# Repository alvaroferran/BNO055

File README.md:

# BNO055
#### 9DOF Absolute orientation sensor

&nbsp;

This repository contains the sensor board and a library for arduino. Both the board and the library are still under development and susceptible of improvement :)

#### BOARD

·The sensor works at 3.3V and can be used through UART or I2C by soldering the PS0 and PS1 pads below, as per the table below:

| PS1        | PS0           | Functionality  |
| ------------- |:-------------:| -----:|
| 0 | 0 | Standard/Fast I2C Interface|
| 0 | 1 |   HID over I2C |
| 1 | 0 |    UART Interface |
| 1 | 1 |    Reserved |

In order to be used with a 5V level microcontroller a 5V-3.3V level shifter must be used.

&nbsp;
·It has two possible, hardware-defined I2C addresses, which are selectable through a solder pad, as in the following table:

| ID PAD       | I2C Address           | ID  |
| ------------- |:-------------:| -----:|
| Not soldered | 0x28 | A |
| Soldered | 0x29 | B  |

&nbsp;

·The "I2C" pad enables the sensor's 4.7k pullup resistors. This pad should only be soldered if there were no other pullup resistors on the bus.

&nbsp;

#### LIBRARY

· To install the library simply copy the folder "BNO055" into your folder "sketchbook/libraries/".

&nbsp;
· In the "examples" subfolder a cheatsheet sketch is available which demonstrates how to read different data.

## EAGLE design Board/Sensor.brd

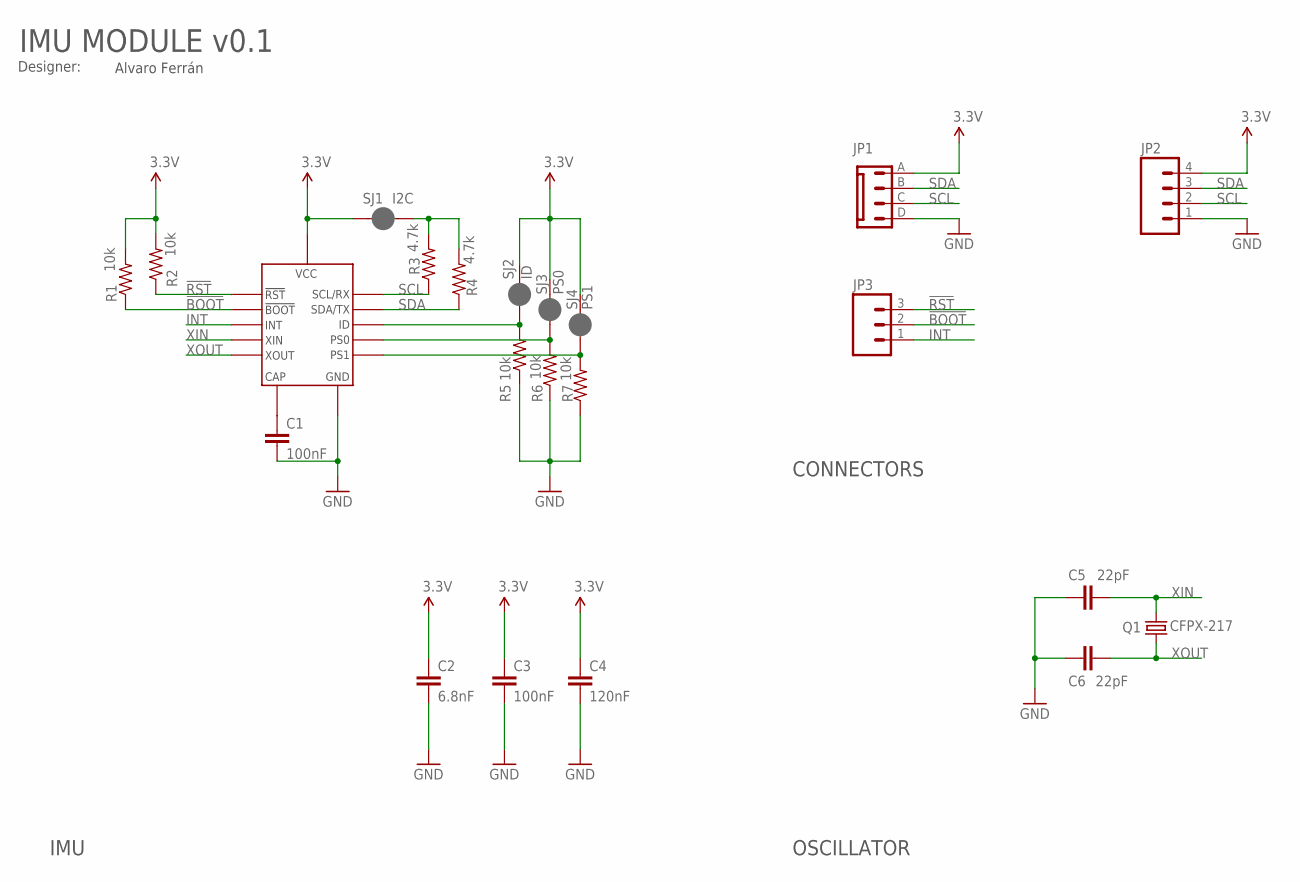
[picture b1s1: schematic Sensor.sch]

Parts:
C1, C3: 100nF; 0603-CAP
C2: 6.8nF; 0603-CAP
C4: 120nF; 0603-CAP
C5, C6: 22pF; 0402-CAP
JP1: MX-6410-04A
JP2: M04LOCK; 1X04_LOCK
JP3: M03LOCK; 1X03_LOCK
Q1: CFPX-217
R1, R2, R5, R6, R7: 10k; 0402-RES
R3, R4: 4.7k; 0402-RES
SJ1: I2C; PAD-JUMPER-2-NC_BY_PASTE_YES_SILK
SJ2: ID; PAD-JUMPER-2-NC_BY_PASTE_YES_SILK
SJ3: PS0; PAD-JUMPER-2-NC_BY_PASTE_YES_SILK
SJ4: PS1; PAD-JUMPER-2-NC_BY_PASTE_YES_SILK
U1: BNO055

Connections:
3.3V: C2.1, C3.1, C4.1, JP1.A, JP2.4, R1.2, R2.2, SJ1.2, SJ2.2, SJ3.2, SJ4.2, U1.3 (VCC), U1.28 (VCC)
!BOOT: JP3.2, R1.1, U1.4 (BOOT)
!RST: JP3.3, R2.1, U1.11 (RST)
GND: C1.2, C2.2, C3.2, C4.2, C5.1, C6.1, JP1.D, JP2.1, R5.1, R6.1, R7.1, U1.2 (GND), U1.10 (GND), U1.15 (GND), U1.16 (GND), U1.18 (GND), U1.25 (GND)
INT: JP3.1, U1.14 (INT)
unnamed: C1.1, U1.9 (CAP)
unnamed: R3.2, R4.2, SJ1.1
unnamed: R5.2, SJ2.1, U1.17 (ID)
unnamed: R6.2, SJ3.1, U1.6 (PS0)
unnamed: R7.2, SJ4.1, U1.5 (PS1)
SCL: JP1.C, JP2.2, R3.1, U1.19 (SCL/RX)
SDA: JP1.B, JP2.3, R4.1, U1.20 (SDA/TX)
XIN: C5.2, Q1.2, U1.27 (XIN)
XOUT: C6.2, Q1.1, U1.26 (XOUT)

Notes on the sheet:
IMU MODULE v0.1
Designer:
Alvaro Ferrán
CONNECTORS
OSCILLATOR
IMU

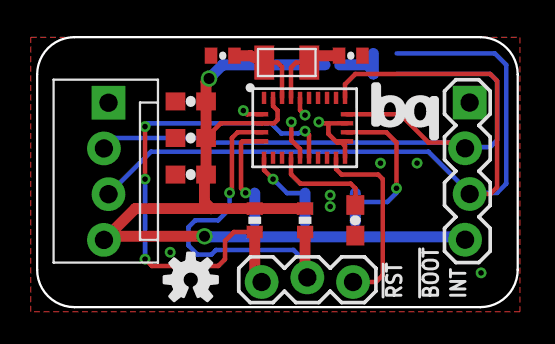
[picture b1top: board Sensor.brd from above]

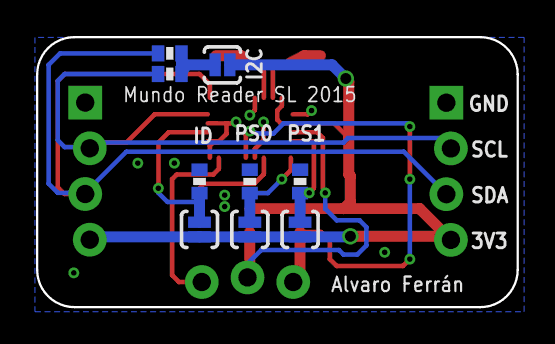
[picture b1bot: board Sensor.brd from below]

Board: 2 copper layers, 26.7 x 15.0 mm, 24 parts (9 on the bottom side), 14 nets.

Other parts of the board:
U$1: BQ_LOGO_MEDIUM
U$2: OSHW-LOGO-S

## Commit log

2015-09-14 Board and library added
2015-10-27 Freecad and PDF added
2016-01-08 AbsAccel and deadReckoning functions added
2016-01-12 Memory optimization
2016-03-14 json added
2017-12-18 Python lib added
2017-12-19 Calibration and self-test result functions added

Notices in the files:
parts and their libraries:
SparkFun-Passives: Licensing: Creative Commons ShareAlike 4.0 International - https://creativecommons.org/licenses/by-sa/4.0
